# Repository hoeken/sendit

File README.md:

This is the hardware design repository for SendIt.

For detailed documentation, please visit the [SendIt documentation](https://sendit.yarrboard.com).

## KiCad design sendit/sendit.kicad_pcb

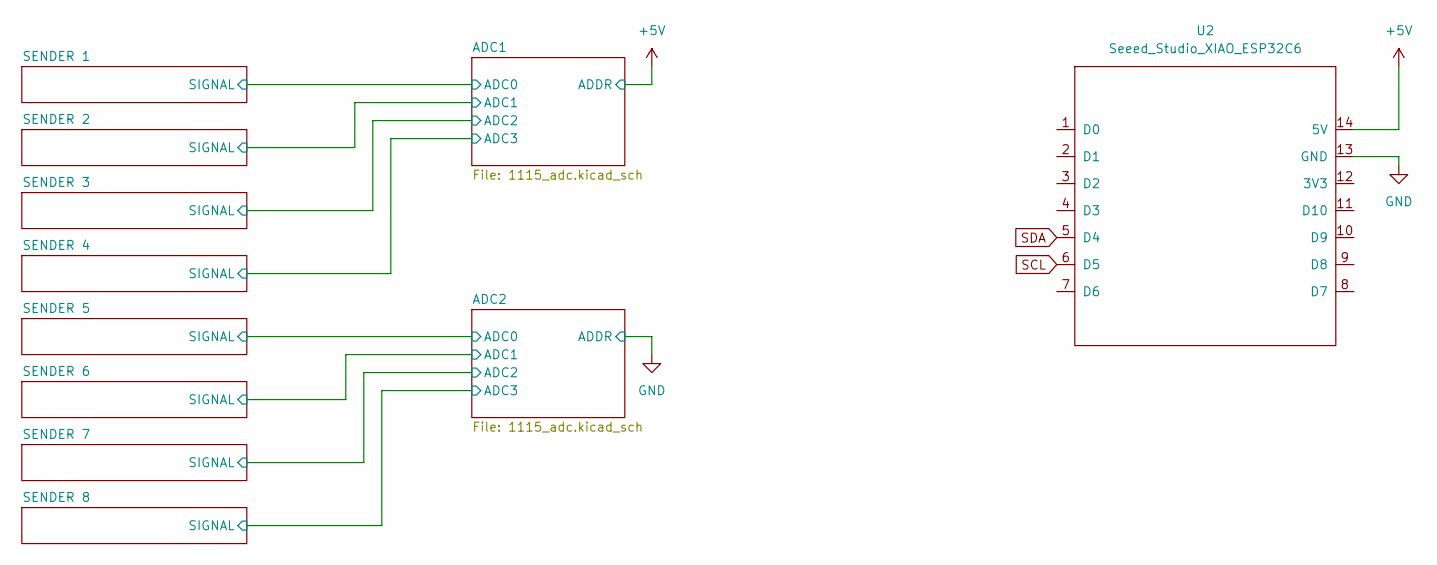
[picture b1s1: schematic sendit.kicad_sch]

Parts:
U2: Seeed_Studio_XIAO_ESP32C6; XIAO-Generic-Hybrid-14P-2.54-21X17.8MM

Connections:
+5V: U2.14 (5V); also elsewhere on the board
GND: U2.13 (GND); also elsewhere on the board
SCL: U2.6 (D5); also elsewhere on the board
SDA: U2.5 (D4); also elsewhere on the board

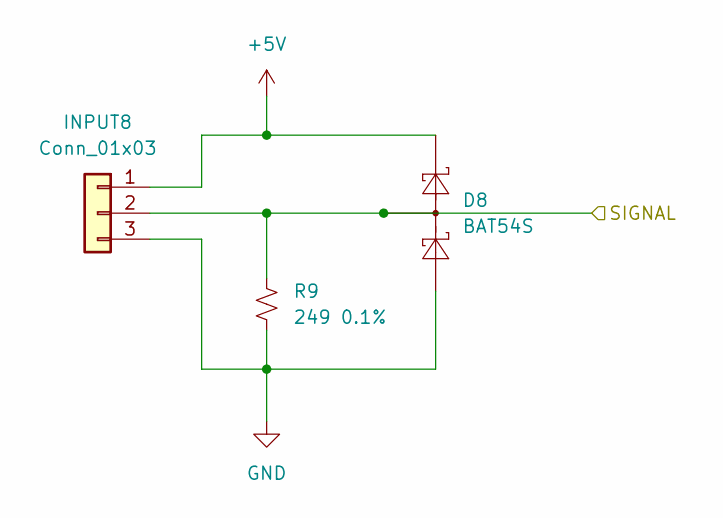
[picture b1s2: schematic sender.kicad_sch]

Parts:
D8: BAT54S; SOT-23; LCSC C727126
INPUT8: Conn_01x03; PhoenixContact_MC_1,5_3-G-3.5_1x03_P3.50mm_Horizontal; LCSC C5188296 and C5188250
R9: 249 0.1%; R_1206_3216Metric_Pad1.30x1.75mm_HandSolder; LCSC C870575

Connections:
+5V: D8.2 (K), INPUT8.1; also elsewhere on the board
/ADC2/ADC3: D8.3 (COM), INPUT8.2, R9.2; also elsewhere on the board
GND: D8.1 (A), INPUT8.3, R9.1; also elsewhere on the board

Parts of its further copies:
D1, D2, D3, D4, D5, D6, D7: BAT54S; SOT-23; LCSC C727126
INPUT1, INPUT2, INPUT3, INPUT4, INPUT5, INPUT6, INPUT7: Conn_01x03; PhoenixContact_MC_1,5_3-G-3.5_1x03_P3.50mm_Horizontal; LCSC C5188296 and C5188250
R1, R3, R4, R5, R6, R7, R8: 249 0.1%; R_1206_3216Metric_Pad1.30x1.75mm_HandSolder; LCSC C870575

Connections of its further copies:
+5V: D1.2 (K), D2.2 (K), D3.2 (K), D4.2 (K), D5.2 (K), D6.2 (K), D7.2 (K), INPUT1.1, INPUT2.1, INPUT3.1, INPUT4.1, INPUT5.1, INPUT6.1, INPUT7.1; also elsewhere on the board
/ADC1/ADC0: D1.3 (COM), INPUT1.2, R1.2; also elsewhere on the board
/ADC1/ADC1: D2.3 (COM), INPUT2.2, R3.2; also elsewhere on the board
/ADC1/ADC2: D3.3 (COM), INPUT3.2, R4.2; also elsewhere on the board
/ADC1/ADC3: D4.3 (COM), INPUT4.2, R5.2; also elsewhere on the board
/ADC2/ADC0: D5.3 (COM), INPUT5.2, R6.2; also elsewhere on the board
/ADC2/ADC1: D6.3 (COM), INPUT6.2, R7.2; also elsewhere on the board
/ADC2/ADC2: D7.3 (COM), INPUT7.2, R8.2; also elsewhere on the board
GND: D1.1 (A), D2.1 (A), D3.1 (A), D4.1 (A), D5.1 (A), D6.1 (A), D7.1 (A), INPUT1.3, INPUT2.3, INPUT3.3, INPUT4.3, INPUT5.3, INPUT6.3, INPUT7.3, R1.1, R3.1, R4.1, R5.1, R6.1, R7.1, R8.1; also elsewhere on the board

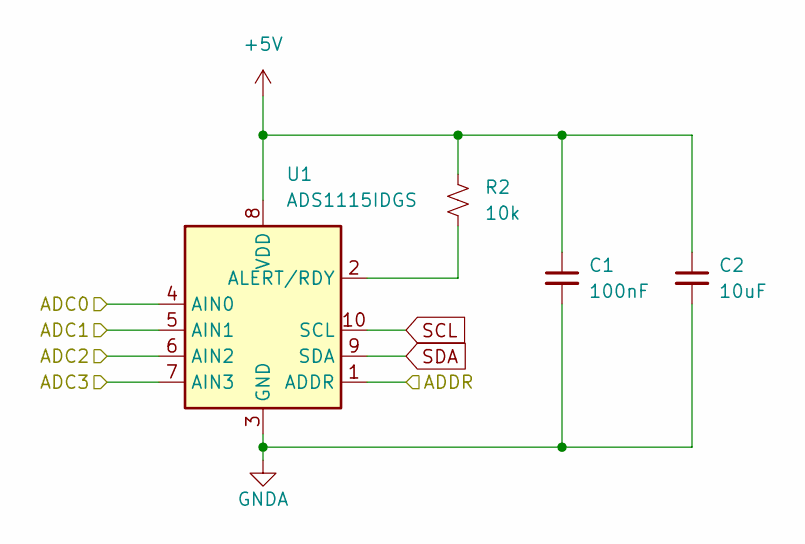
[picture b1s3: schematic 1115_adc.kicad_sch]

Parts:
C1: 100nF; C_0805_2012Metric_Pad1.18x1.45mm_HandSolder; LCSC C49678
C2: 10uF; C_0805_2012Metric_Pad1.18x1.45mm_HandSolder; LCSC C1952580
R2: 10k; R_0805_2012Metric_Pad1.20x1.40mm_HandSolder; LCSC C84376
U1: ADS1115IDGS; TSSOP-10_3x3mm_P0.5mm

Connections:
+5V: C1.1, C2.1, R2.2, U1.1 (ADDR), U1.8 (VDD); also elsewhere on the board
/ADC1/ADC0: U1.4 (AIN0); also elsewhere on the board
/ADC1/ADC1: U1.5 (AIN1); also elsewhere on the board
/ADC1/ADC2: U1.6 (AIN2); also elsewhere on the board
/ADC1/ADC3: U1.7 (AIN3); also elsewhere on the board
GNDA: C1.2, C2.2, U1.3 (GND); also elsewhere on the board
unnamed: R2.1, U1.2 (ALERT/RDY)
SCL: U1.10 (SCL); also elsewhere on the board
SDA: U1.9 (SDA); also elsewhere on the board

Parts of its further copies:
C3: 100nF; C_0805_2012Metric_Pad1.18x1.45mm_HandSolder; LCSC C49678
C4: 10uF; C_0805_2012Metric_Pad1.18x1.45mm_HandSolder; LCSC C1952580
R10: 10k; R_0805_2012Metric_Pad1.20x1.40mm_HandSolder; LCSC C84376
U3: ADS1115IDGS; TSSOP-10_3x3mm_P0.5mm

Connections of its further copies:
+5V: C3.1, C4.1, R10.2, U3.8 (VDD); also elsewhere on the board
/ADC2/ADC0: U3.4 (AIN0); also elsewhere on the board
/ADC2/ADC1: U3.5 (AIN1); also elsewhere on the board
/ADC2/ADC2: U3.6 (AIN2); also elsewhere on the board
/ADC2/ADC3: U3.7 (AIN3); also elsewhere on the board
GND: U3.1 (ADDR); also elsewhere on the board
GNDA: C3.2, C4.2, U3.3 (GND); also elsewhere on the board
unnamed: R10.1, U3.2 (ALERT/RDY)
SCL: U3.10 (SCL); also elsewhere on the board
SDA: U3.9 (SDA); also elsewhere on the board

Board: 2 copper layers, 33 parts (0 on the bottom side), 15 nets, no tracks yet.

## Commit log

2024-08-19 gitignore
2024-08-19 updated schematic.
2026-04-11 stubbed readme
2026-04-15 added rev c case
